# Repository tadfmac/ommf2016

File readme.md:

# OMMF2016 

[ogaki mini maker faire 2016](http://ommf.iamas.ac.jp/)で[CHIRIMEN Open Hardwareコミュニティ](https://github.com/chirimen-oh)の展示作品群の１つとして展示した「くだもの触って光ったり鳴ったり」のソースコードです。

## cheen-rimen

CHIRIMEN用シールド「CHEEN-RIMEN」のデータです。
CHEEN-RIMENはダイソーで販売している「呼び鈴ベル（通称：ちーん）」を搭載することができるシールドです。呼び鈴を手動で鳴らした時の情報をCHIRIMEN側にI2C経由で伝えることができます。また搭載した呼び鈴はソレノイドで鳴動することもできます。
さらにボリューム調整機能つきオーディオ出力端子や4つのGPIO端子、切り替えつき外部電源端子、4つの外部負荷付きタッチセンサー端子など豊富な機能をCHIRIMENに拡張可能です。

ここで公開する情報には、eagleファイルと、CHEEN-RIMENに搭載されたATmega8A用のファームウエア（Arduino Sketch）が含まれています。

## cont

スマホをコントローラにするWebアプリです。
ボタンを押すことでommfapp側にアヒルを投げ込みます。

## ommfapp

CHIRIMEN用のアプリです。タッチセンサー（に繋いだくだものや野菜など）を触ることでクリスマスツリーにオーナメントを飾り付けしながら「ちーん」音を鳴らします。GPIOに繋がったサンタも光ります。また、contのボタンが押された時にアヒルが飛んできます。

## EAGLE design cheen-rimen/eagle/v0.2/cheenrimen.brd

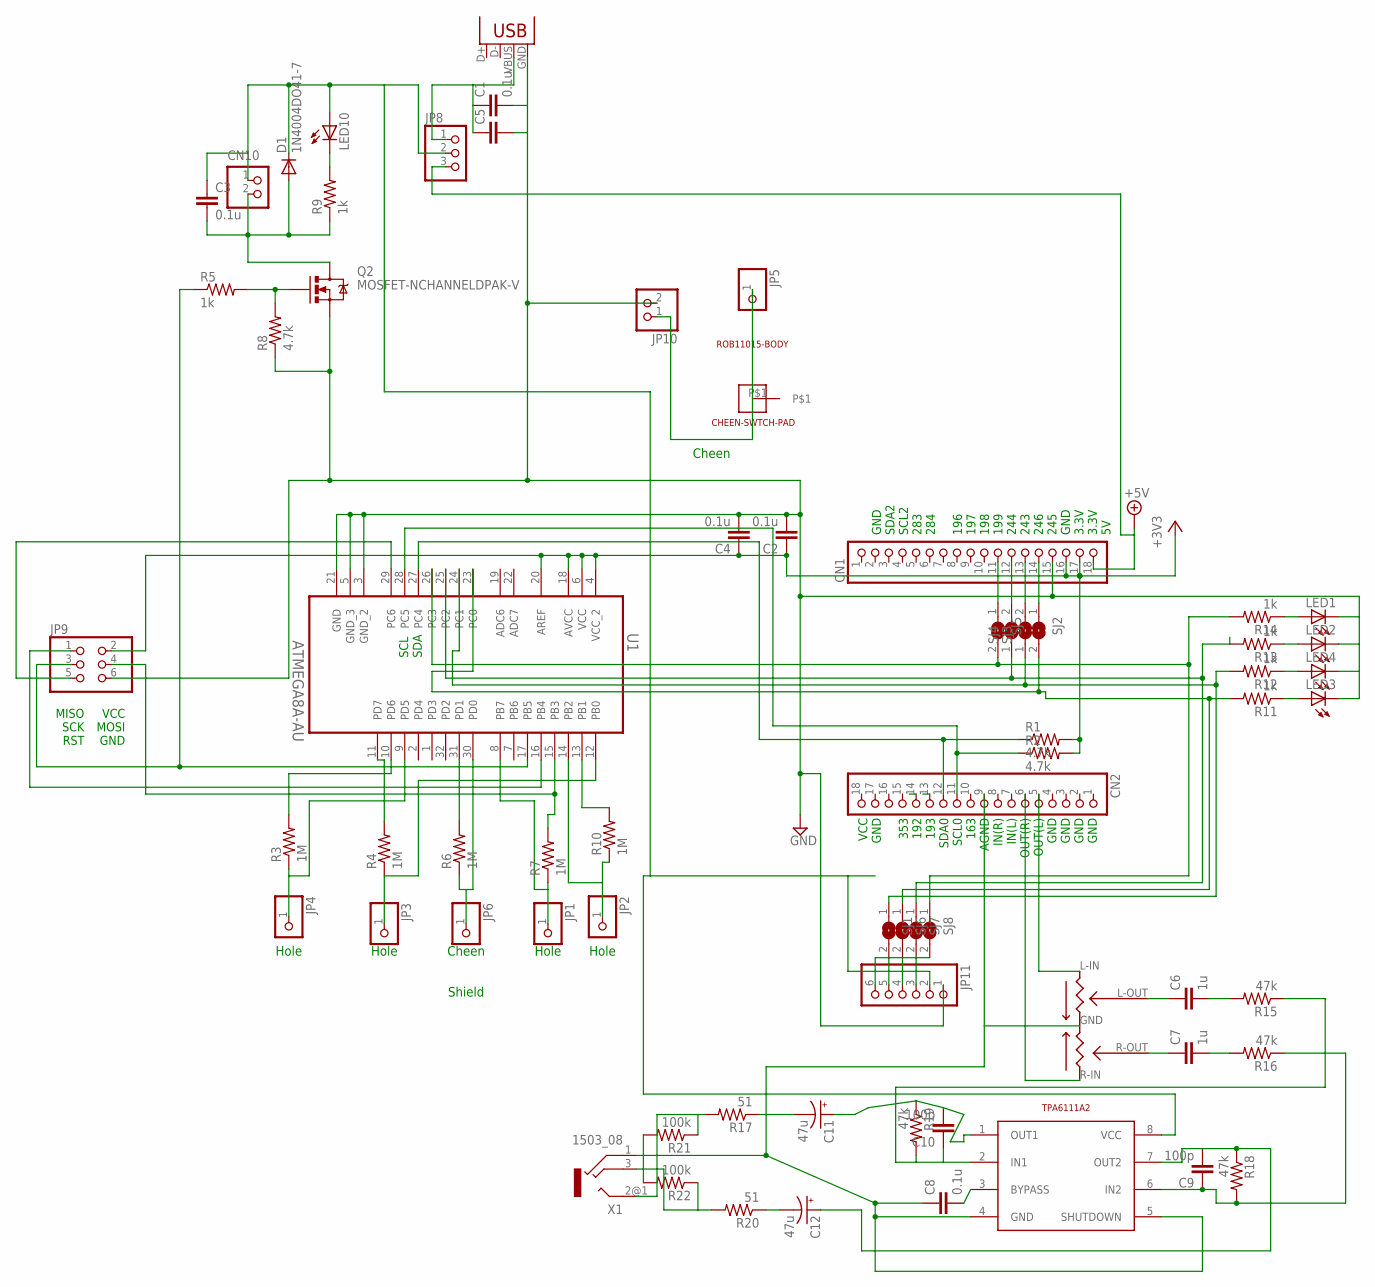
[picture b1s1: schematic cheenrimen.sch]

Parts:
C1, C2, C3, C4, C8: 0.1u; C0603K
C5: C-EUC0805; C0805
C6, C7: 1u; C0603K
C9, C10: 100p; C0603K
C11, C12: 47u; 153CLV-0605
CN1, CN2: PINHD-1X18; 1X18
CN10: B2B-PH-K-S
D1: 1N4004DO41-7; DO41-7.6
JP1, JP2, JP3, JP4: PINHD-1X15MM; 1X01-LARGE
JP5, JP6: PINHD-1X1NORMAL; 1X01-S
JP7: USB-MICROB
JP8: PINHD-1X3; 1X03
JP9: PINHD-2X3; 2X03
JP10: PINHD-1X2; 1X02
JP11: PINHD-1X6; 1X06
LED1, LED2, LED3, LED4: LEDSML0805; SML0805
LED10: LED3MM
Q2: MOSFET-NCHANNELDPAK-V; DPAK-V
R1, R2, R8: 4.7k; R0603
R3, R4, R6, R7, R10: 1M; R0805
R5, R9, R11, R12, R13, R14: 1k; R0603
R15, R16, R18, R19: 47k; R0603
R17, R20: 51; R0603
R21, R22: 100k; R0603
SJ1, SJ2, SJ3, SJ4, SJ5, SJ6, SJ7, SJ8: SJ
U1: ATMEGA8A-AU; QFP80P900X900X120-32N
U$2: CHEEN-SWITCH-PAD
U$3: ROB11015-BODY; SOLENOID-ROB11015-BODY
U$4: 5PIN-RADIO-POT
U$5: TPA6111A2; MSOP8
X1: 1503_08

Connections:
+3V3: C2.1, C4.1, CN1.16, CN1.17, JP9.2, R1.2, R2.2, U1.4 (VCC_2), U1.6 (VCC), U1.18 (AVCC), U1.20 (AREF)
+5V: CN1.18, JP8.3
+5V/1: C3.1, CN10.1, D1.C, JP8.2, JP11.2, LED10.A, U$5.8 (VCC)
AGND: C8.1, CN2.9, R21.2, R22.2, U$4.GND, U$5.4 (GND), U$5.5 (SHUTDOWN), X1.1 (GND)
GND: C1.2, C2.2, C4.2, C5.2, CN1.15, JP7.GND, JP9.6, JP10.2, JP11.1, LED1.C, LED2.C, LED3.C, LED4.C, Q2.P$3 (S), R8.1, U1.3 (GND_2), U1.5 (GND_3), U1.21 (GND)
unnamed: C1.1, C5.1, JP7.VBUS, JP8.1
unnamed: JP9.1, U1.16 (PB4)
unnamed: CN1.14, SJ2.1
unnamed: CN1.13, SJ3.2
unnamed: CN1.12, SJ4.2
unnamed: JP5.1, JP10.1, U$2.P$1
unnamed: CN2.11, R2.1, U1.28 (PC5)
unnamed: JP9.3, R5.1, U1.17 (PB5)
unnamed: CN2.12, R1.1, U1.27 (PC4)
unnamed: R3.2, U1.10 (PD6)
unnamed: JP4.1, R3.1, U1.9 (PD5)
unnamed: CN1.11, SJ5.1
unnamed: Q2.P$1 (G), R5.2, R8.2
unnamed: C3.2, CN10.2, D1.A, Q2.P$2 (D), R9.1
unnamed: R6.2, U1.31 (PD1)
unnamed: LED10.K (C), R9.2
unnamed: JP2.1, R10.1, U1.14 (PB2)
unnamed: R4.2, U1.11 (PD7)
unnamed: JP3.1, R4.1, U1.12 (PB0)
unnamed: R10.2, U1.13 (PB1)
unnamed: JP6.1, R6.1, U1.30 (PD0)
unnamed: JP9.4, R7.2, U1.15 (PB3)
unnamed: JP1.1, R7.1, U1.8 (PB7)
unnamed: JP9.5, U1.29 (PC6)
unnamed: R14.2, SJ5.2, SJ8.1, U1.26 (PC3)
unnamed: R13.2, SJ4.1, SJ7.1, U1.25 (PC2)
unnamed: R12.2, SJ1.1, SJ3.1, U1.24 (PC1)
unnamed: R11.2, SJ2.2, SJ6.1, U1.23 (PC0)
unnamed: LED1.A, R14.1
unnamed: LED2.A, R13.1
unnamed: LED4.A, R12.1
unnamed: LED3.A, R11.1
unnamed: JP11.6, SJ1.2
unnamed: JP11.5, SJ6.2
unnamed: JP11.4, SJ7.2
unnamed: JP11.3, SJ8.2
unnamed: R17.2, R21.1, X1.2@1 (L)
unnamed: CN2.5, U$4.L-IN (IN-L)
unnamed: CN2.6, U$4.R-IN (IN-R)
unnamed: C6.1, U$4.L-OUT (OUT-L)
unnamed: C7.1, U$4.R-OUT (OUT-R)
unnamed: C6.2, R15.2
unnamed: C7.2, R16.2
unnamed: C10.1, R15.1, R19.2, U$5.2 (IN1)
unnamed: C9.1, R16.1, R18.2, U$5.6 (IN2)
unnamed: C11.-, R17.1
unnamed: C8.2, U$5.3 (BYPASS)
unnamed: C9.2, C12.+, R18.1, U$5.7 (OUT2)
unnamed: C10.2, C11.+, R19.1, U$5.1 (OUT1)
unnamed: R20.2, R22.1, X1.3 (R)
unnamed: C12.-, R20.1

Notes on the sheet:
Hole
Cheen
Shield
VCC GND 353 192 193 SDA0 SCL0 163 AGND IN(R) IN(L) OUT(R) OUT(L) GND GND GND GND
GND SDA2 SCL2 283 284 196 197 198 199 244 243 246 245 GND 3.3V 3.3V 5V
SCL
SDA
MISO SCK RST
VCC MOSI GND

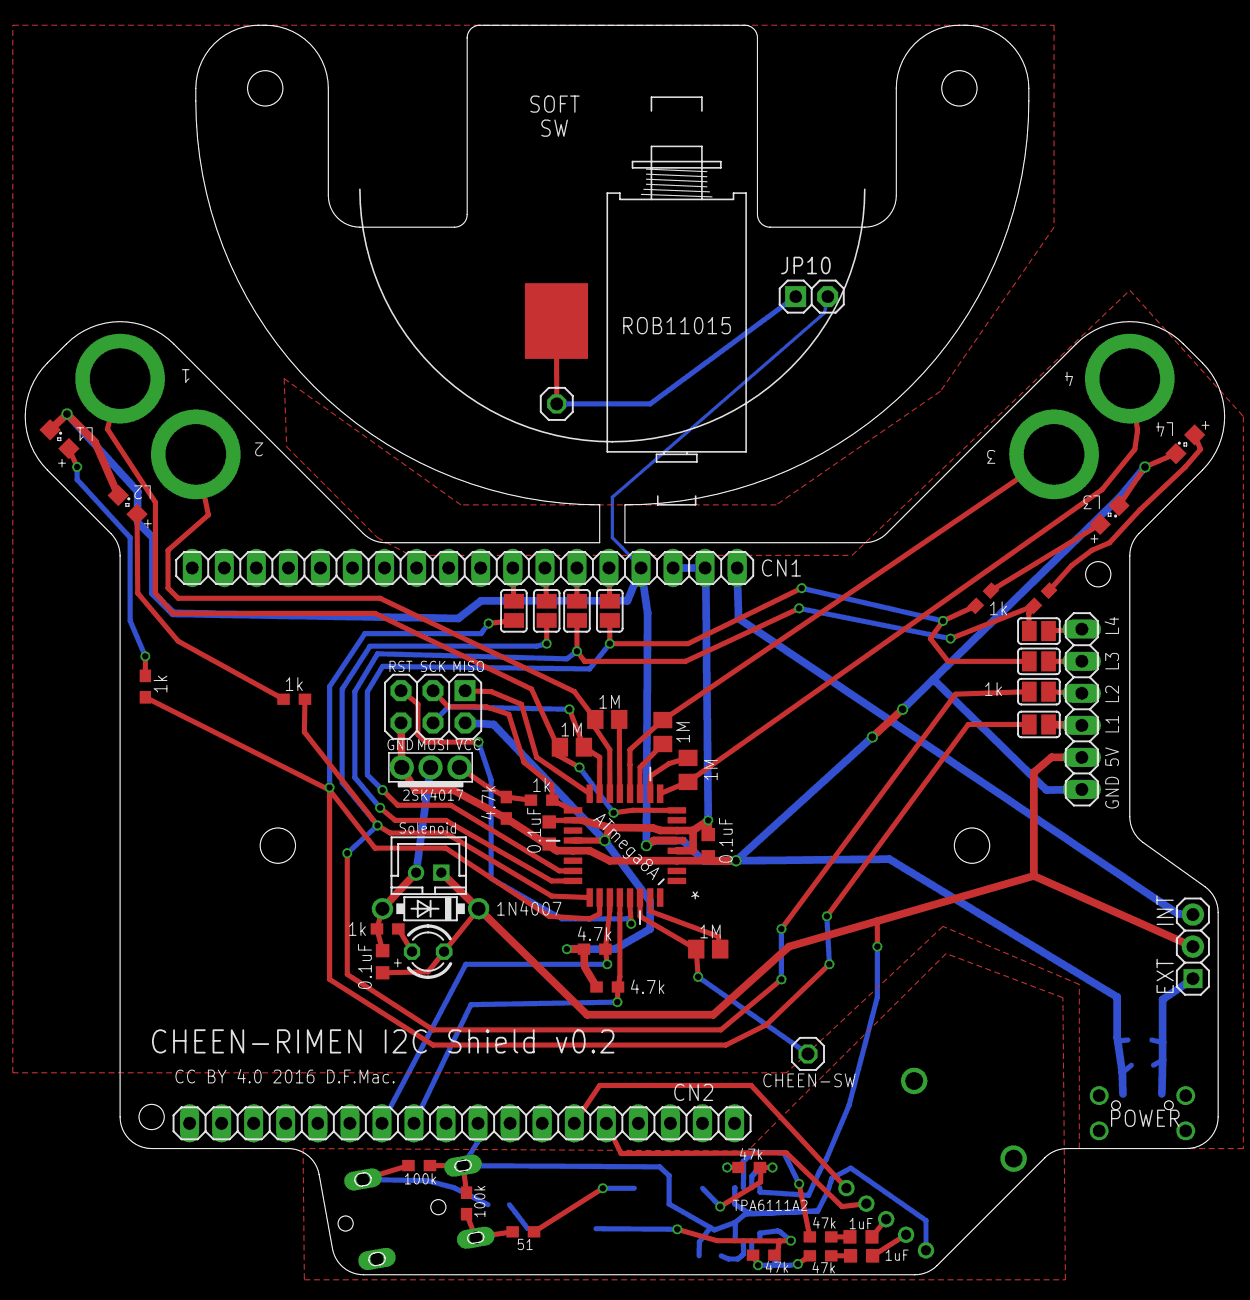
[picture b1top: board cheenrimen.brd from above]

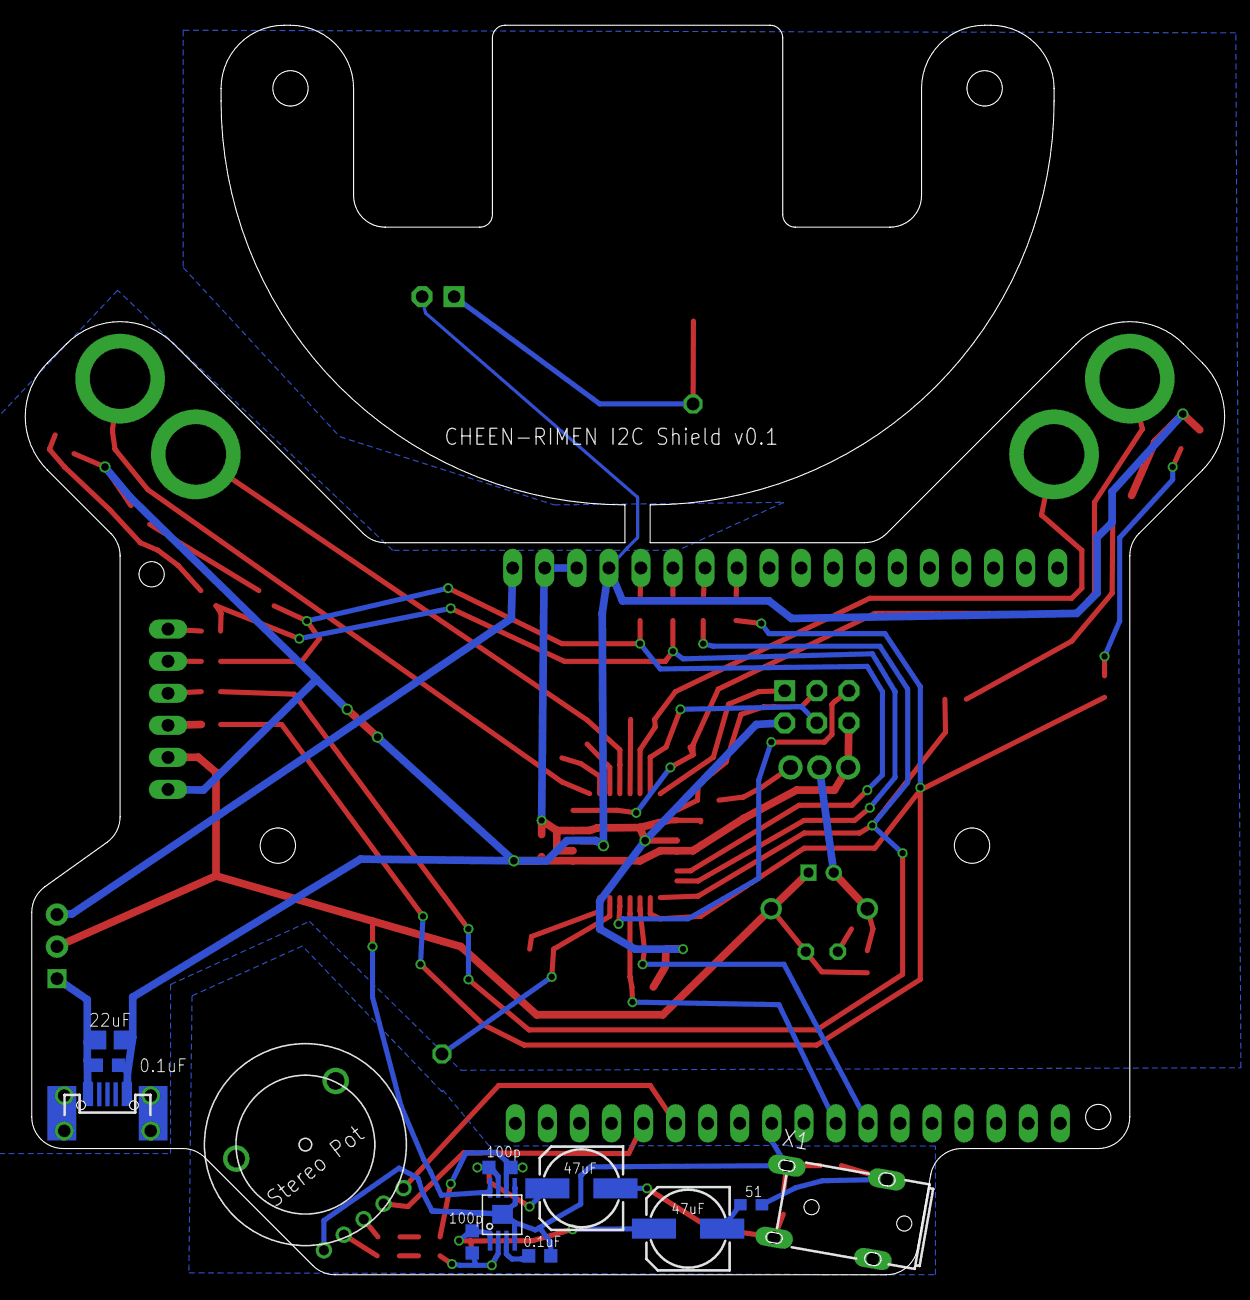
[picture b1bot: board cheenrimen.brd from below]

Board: 2 copper layers, 95.0 x 99.0 mm, 69 parts (12 on the bottom side), 56 nets.

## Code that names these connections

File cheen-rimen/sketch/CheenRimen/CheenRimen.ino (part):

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###########################################
# ATmega8A
#
# 25:PC2/ADC2/●D16(LED2)---------------+
# 26:PC3/ADC3/●D17(LED1)-------------+ |
# 27:PC4/ADC4/SDA/●D18(SDA)--------+ | |
# 28:PC5/ADC5/SCL/●D19(SCL)------+ | | | 
# 29:PC6/RESET       ----------+ | | | |
# 30:PD0/RXD/●D0(SOT5-CH)----+ | | | | |
# 31:PD1/TXD/●D1(SIN5-CH)--+ | | | | | |
# 32:PD2/INT0/●D2   -----+ | | | | | | |
#                      +-+-+-+-+-+-+-+-+-+
# 01:PD3/INT1/●D3      | ●               | 24:PC1/ADC1/●D15(LED4)
# 02:PD4/XCK/T0/●D4    |                 | 23:PC0/ADC0/●D14(LED3)
# 03:GND               |                 | 22:ADC7
# 04:VCC               |                 | 21:GND
# 05:GND               |                 | 20:AREF
# 06:VCC               |                 | 19:ADC6
# 07:PB6/XTAL1         |                 | 18:AVCC
# 08:PB7/XTAL2(SIN-1)  |                 | 17:PB5/SCK/●D13(CHEEN OUT)
#                      +-+-+-+-+-+-+-+-+-+
# 09:PD5/●D5(SIN-4) -----+ | | | | | | |
# 10:PD6/●D6(SOT-4) -------+ | | | | | |
# 11:PD7/●D7(SOT-3)  --------+ | | | | |
# 12:PB0/●D8(SIN-3)  ----------+ | | | |
# 13:PB1/OC1A/●D9(SOT-2)---------+ | | | 
# 14:PB2/SS/OC1B/●D10(SIN-2)-------+ | |
# 15:PB3/MOSI/OC2/●D11(SOT-1)--------+ |
# 16:PB4/MISO/●D12---------------------+
#
###########################################

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}REG_DATA_STR;

REG_DATA_STR Leds[LEDNUM] = {
  {(uint8_t *)_SFR_ADDR(DDRC),(uint8_t *)_SFR_ADDR(PORTC),NULL,PC3,0},
  {(uint8_t *)_SFR_ADDR(DDRC),(uint8_t *)_SFR_ADDR(PORTC),NULL,PC2,0},
  {(uint8_t *)_SFR_ADDR(DDRC),(uint8_t *)_SFR_ADDR(PORTC),NULL,PC0,0},
  {(uint8_t *)_SFR_ADDR(DDRC),(uint8_t *)_SFR_ADDR(PORTC),NULL,PC1,0}
};

void Led_Init(){}
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}

void Led_AllOn(void){
  DDRC |= ((1 << PC3)|(1 << PC2)|(1 << PC0)|(1 << PC1));
  PORTC |= ((1 << PC3)|(1 << PC2)|(1 << PC0)|(1 << PC1));
}

void Led_AllOff(void){
  PORTC &= ~((1 << PC3)|(1 << PC2)|(1 << PC0)|(1 << PC1));
  DDRC &= ~((1 << PC3)|(1 << PC2)|(1 << PC0)|(1 << PC1));
}


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#define SENSOR_CALIB_TIMES   64

REG_DATA_STR SensorOuts[SENSORNUM] = {
  {(uint8_t *)_SFR_ADDR(DDRB),(uint8_t *)_SFR_ADDR(PORTB),NULL,PB3,0},
  {(uint8_t *)_SFR_ADDR(DDRB),(uint8_t *)_SFR_ADDR(PORTB),NULL,PB1,0},
  {(uint8_t *)_SFR_ADDR(DDRD),(uint8_t *)_SFR_ADDR(PORTD),NULL,PD7,0},
  {(uint8_t *)_SFR_ADDR(DDRD),(uint8_t *)_SFR_ADDR(PORTD),NULL,PD6,0},
  {(uint8_t *)_SFR_ADDR(DDRD),(uint8_t *)_SFR_ADDR(PORTD),NULL,PD1,0}
};

REG_DATA_STR SensorIns[SENSORNUM] = {
  {(uint8_t *)_SFR_ADDR(DDRB),NULL,(uint8_t *)_SFR_ADDR(PINB),PB7,0},
  {(uint8_t *)_SFR_ADDR(DDRB),NULL,(uint8_t *)_SFR_ADDR(PINB),PB2,0},
  {(uint8_t *)_SFR_ADDR(DDRB),NULL,(uint8_t *)_SFR_ADDR(PINB),PB0,0},
  {(uint8_t *)_SFR_ADDR(DDRD),NULL,(uint8_t *)_SFR_ADDR(PIND),PD5,0},
  {(uint8_t *)_SFR_ADDR(DDRD),NULL,(uint8_t *)_SFR_ADDR(PIND),PD0,0}
};

#define SENSOR_MARGIN   8
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uint8_t cntCheen = 0;
uint8_t maxCheenCnt = DEFAULT_MAX_CHEEN_CNT;

#define CheenInit() (DDRB |= (1 << PB5))
#define CheenOn() (PORTB |= (1 << PB5))
#define CheenOff() (PORTB &= ~(1 << PB5))

void CheenStart(){
  Led_On(3);
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
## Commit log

2017-03-22 1st commit
2017-03-22 add image
2017-03-22 fix readme.md

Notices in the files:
cheen-rimen/eagle/v0.2/cheenrimen.brd:
CC BY 4.0 2016 D.F.Mac.
